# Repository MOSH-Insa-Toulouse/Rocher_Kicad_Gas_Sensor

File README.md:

# Maxime Rocher Compte Rendu Gas Sensor sur KICAD

### Introduction

  Dans le cadre du module Smart Devices de notre formation Innovative Smart System, nous avons été chargés de concevoir un circuit électronique avec le logiciel Kicad. Ce circuit électronique devait être basé sur un shield Arduino et intégrer un capteur de gaz pour  pouvoir ensuite communiquer les valeurs récupérer sur un réseau LORA. Ce dossier contient les résultats de la conception sous Kicad.

### Schématique

### Layout du circuit imprimé

### Visualisation 3D

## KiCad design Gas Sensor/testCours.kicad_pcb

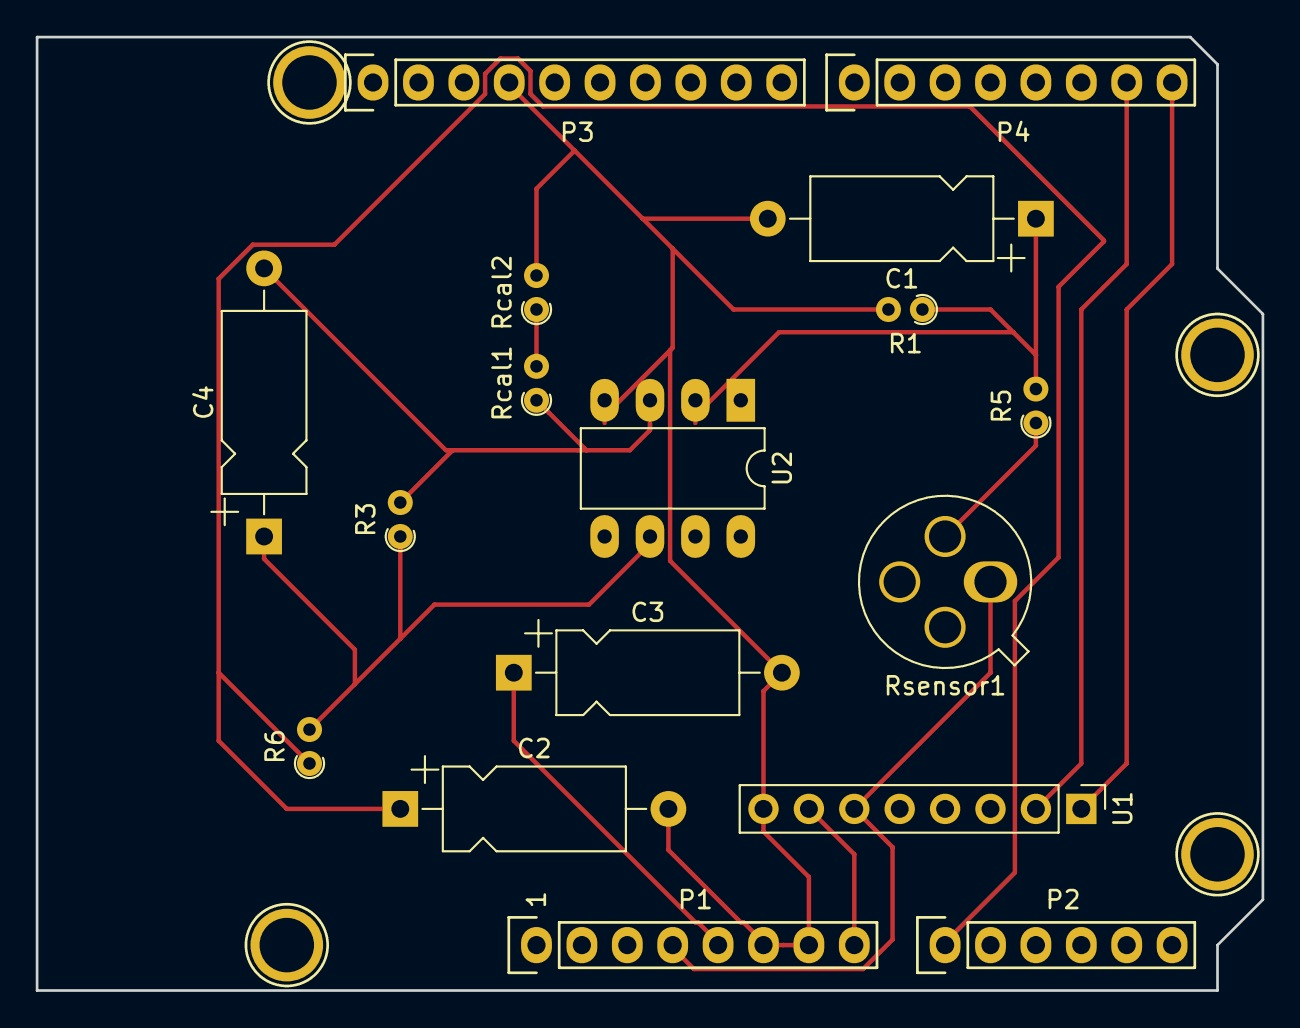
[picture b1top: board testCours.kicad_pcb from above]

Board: 2 copper layers, 68.6 x 53.3 mm, 21 parts (0 on the bottom side), 14 nets.

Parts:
C1, C2, C3: 100n; CP_Axial_L10.0mm_D4.5mm_P15.00mm_Horizontal
C4: 1u; CP_Axial_L10.0mm_D4.5mm_P15.00mm_Horizontal
P1: Power; Socket_Strip_Arduino_1x08
P2: Analog; Socket_Strip_Arduino_1x06
P3: Digital; Socket_Strip_Arduino_1x10
P4: Digital; Socket_Strip_Arduino_1x08
P5, P6, P7, P8: CONN_01X01; Arduino_1pin
R1, R3: 100k; R_Axial_DIN0204_L3.6mm_D1.6mm_P1.90mm_Vertical
R5: 10k; R_Axial_DIN0204_L3.6mm_D1.6mm_P1.90mm_Vertical
R6: 1k; R_Axial_DIN0204_L3.6mm_D1.6mm_P1.90mm_Vertical
Rcal1, Rcal2: R; R_Axial_DIN0204_L3.6mm_D1.6mm_P1.90mm_Vertical
Rsensor1: 10k<...<1G; TO-5-4
U1: RN2483BREAKOUT; PinHeader_1x08_P2.54mm_Vertical
U2: LTC1050; DIP-8_W7.62mm_LongPads

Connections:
+3V3: P1.4, Rsensor1.1, U1.6
+5V: C3.1, P1.5
/0(Rx): P4.8, U1.1
/1(Tx): P4.7, U1.2
/A0: C2.1, P2.1, R6.1
/A4(SDA): P2.5, P3.2
/A5(SCL): P2.6, P3.1
/Vin: P1.8, U1.7
GND: C1.2, C2.2, C3.2, P1.6, P1.7, P3.4, R1.2, Rcal2.2, U1.8, U2.4
unnamed: C1.1, R1.1, R5.2, U2.2
unnamed: C4.1, R3.1, R6.2, U2.6
unnamed: C4.2, R3.2, Rcal1.1, U2.3
unnamed: R5.1, Rsensor1.2
unnamed: Rcal1.2, Rcal2.1
